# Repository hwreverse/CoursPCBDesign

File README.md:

# CoursPCBDesign
Sources pour les séquences de cours sur Twitch/Youtube (Alexx_and_seb) sur le PCB Design

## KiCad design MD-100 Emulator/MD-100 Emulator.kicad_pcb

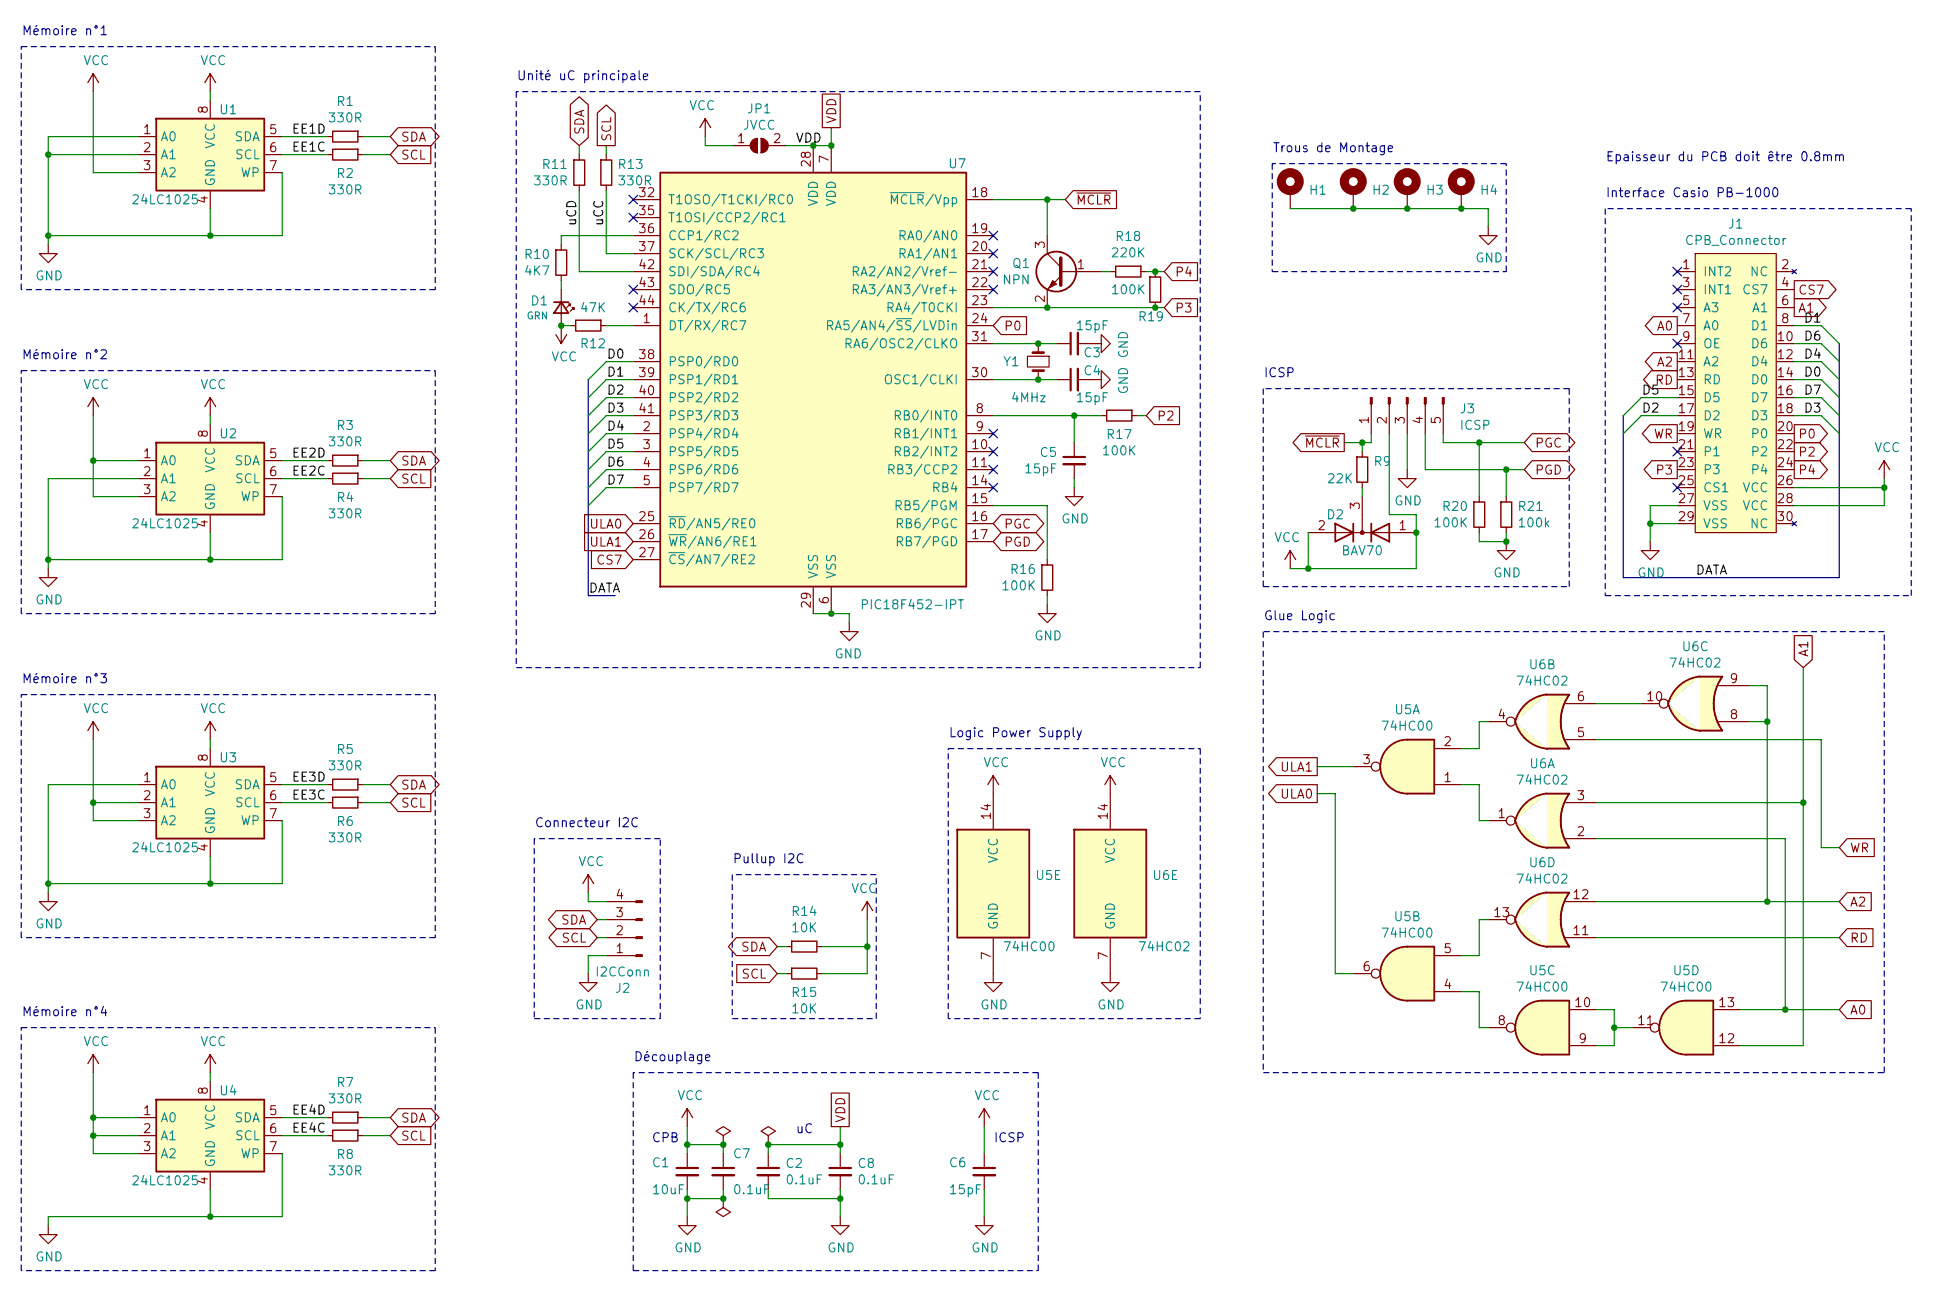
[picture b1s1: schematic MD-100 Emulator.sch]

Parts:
C1: 10uF; C_0805_2012Metric_Pad1.15x1.40mm_HandSolder
C2, C7, C8: 0.1uF; C_0805_2012Metric_Pad1.15x1.40mm_HandSolder
C3, C4, C5, C6: 15pF; C_0805_2012Metric_Pad1.15x1.40mm_HandSolder
D1: GRN; LED_0805_2012Metric_Pad1.15x1.40mm_HandSolder
D2: BAV70; SOT-23
H1, H2, H3, H4: MountingHole_Pad; MountingHole_3.2mm_M3_Pad_Via
J1: CPB_Connector; Connector_Casio_2x15_1.27_SYSBUS
J2: I2CConn; PinHeader_1x04_P2.54mm_Horizontal
J3: ICSP; PinHeader_1x05_P2.54mm_Horizontal
JP1: JVCC; SolderJumper-2_P1.3mm_Open_RoundedPad1.0x1.5mm
Q1: NPN; SOT-23
R1, R2, R3, R4, R5, R6, R7, R8, R11, R13: 330R; R_0805_2012Metric_Pad1.15x1.40mm_HandSolder
R9: 22K; R_0805_2012Metric_Pad1.15x1.40mm_HandSolder
R10: 4K7; R_0805_2012Metric_Pad1.15x1.40mm_HandSolder
R12: 47K; R_0805_2012Metric_Pad1.15x1.40mm_HandSolder
R14, R15: 10K; R_0805_2012Metric_Pad1.15x1.40mm_HandSolder
R16, R17, R19, R20: 100K; R_0805_2012Metric_Pad1.15x1.40mm_HandSolder
R18: 220K; R_0805_2012Metric_Pad1.15x1.40mm_HandSolder
R21: 100k; R_0805_2012Metric_Pad1.15x1.40mm_HandSolder
U1, U2, U3, U4: 24LC1025; SOIC-8_3.9x4.9mm_P1.27mm
U5: 74HC00; SOIC-14_3.9x8.7mm_P1.27mm
U6: 74HC02; SOIC-14_3.9x8.7mm_P1.27mm
U7: PIC18F452-IPT; TQFP-44_10x10mm_P0.8mm
Y1: 4MHz; Crystal_SMD_HC49-SD_HandSoldering

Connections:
/D0: J1.14 (D0), U7.38 (PSP0/RD0)
/D1: J1.8 (D1), U7.39 (PSP1/RD1)
/D2: J1.17 (D2), U7.40 (PSP2/RD2)
/D3: J1.18 (D3), U7.41 (PSP3/RD3)
/D4: J1.12 (D4), U7.2 (PSP4/RD4)
/D5: J1.15 (D5), U7.3 (PSP5/RD5)
/D6: J1.10 (D6), U7.4 (PSP6/RD6)
/D7: J1.16 (D7), U7.5 (PSP7/RD7)
/EE1C: R2.2, U1.6 (SCL)
/EE1D: R1.2, U1.5 (SDA)
/EE2C: R4.2, U2.6 (SCL)
/EE2D: R3.2, U2.5 (SDA)
/EE3C: R6.2, U3.6 (SCL)
/EE3D: R5.2, U3.5 (SDA)
/EE4C: R8.2, U4.6 (SCL)
/EE4D: R7.2, U4.5 (SDA)
/uCC: R13.2, U7.37 (SCK/SCL/RC3)
/uCD: R11.2, U7.42 (SDI/SDA/RC4)
A0: J1.7 (A0), U5.13, U6.2
A1: J1.6 (A1), U5.12, U6.3
A2: J1.11 (A2), U6.8, U6.9, U6.12
CS7: J1.4 (CS7), U7.27 (~CS~/AN7/RE2)
GND: C1.2, C2.2, C3.2, C4.2, C5.2, C6.2, C7.2, C8.2, H1.1, H2.1, H3.1, H4.1, J1.27 (VSS), J1.29 (VSS), J2.1, J3.3, R16.2, R20.2, R21.2, U1.1 (A0), U1.2 (A1), U1.4 (GND), U1.7 (WP), U2.2 (A1), U2.4 (GND), U2.7 (WP), U3.1 (A0), U3.4 (GND), U3.7 (WP), U4.4 (GND), U4.7 (WP), U5.7 (GND), U6.7 (GND), U7.6 (VSS), U7.29 (VSS)
unnamed: C3.1, U7.31 (RA6/OSC2/CLKO), Y1.1
unnamed: C4.1, U7.30 (OSC1/CLKI), Y1.2
unnamed: C5.1, R17.2, U7.8 (RB0/INT0)
unnamed: D1.1 (K), R10.2
unnamed: D2.3 (K), R9.2
unnamed: Q1.1 (B), R18.2
unnamed: R10.1, U7.36 (CCP1/RC2)
unnamed: R12.1, U7.1 (DT/RX/RC7)
unnamed: R16.1, U7.15 (RB5/PGM)
unnamed: U5.1, U6.1
unnamed: U5.2, U6.4
unnamed: U5.4, U5.8
unnamed: U5.5, U6.13
unnamed: U5.9, U5.10, U5.11
unnamed: U6.6, U6.10
P0: J1.20 (P0), U7.24 (RA5/AN4/~SS~/LVDin)
P2: J1.22 (P2), R17.1
P3: J1.23 (P3), Q1.2 (E), R19.2, U7.23 (RA4/T0CKI)
P4: J1.24 (P4), R18.1, R19.1
PGC: J3.5, R20.1, U7.16 (RB6/PGC)
PGD: J3.4, R21.1, U7.17 (RB7/PGD)
RD: J1.13 (RD), U6.11
SCL: J2.2, R2.1, R4.1, R6.1, R8.1, R13.1, R15.1
SDA: J2.3, R1.1, R3.1, R5.1, R7.1, R11.1, R14.1
ULA0: U5.6, U7.25 (~RD~/AN5/RE0)
ULA1: U5.3, U7.26 (~WR~/AN6/RE1)
VCC: C1.1, C6.1, C7.1, D1.2 (A), D2.1 (A), D2.2 (A), J1.26 (VCC), J1.28 (VCC), J2.4, J3.2, JP1.1 (A), R12.2, R14.2, R15.2, U1.3 (A2), U1.8 (VCC), U2.1 (A0), U2.3 (A2), U2.8 (VCC), U3.2 (A1), U3.3 (A2), U3.8 (VCC), U4.1 (A0), U4.2 (A1), U4.3 (A2), U4.8 (VCC), U5.14 (VCC), U6.14 (VCC)
VDD: C2.1, C8.1, JP1.2 (B), U7.7 (VDD), U7.28 (VDD)
WR: J1.19 (WR), U6.5
~MCLR: J3.1, Q1.3 (C), R9.1, U7.18 (~MCLR~/Vpp)

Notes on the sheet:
Mémoire n°1
Mémoire n°2
Mémoire n°3
Mémoire n°4
Glue Logic
Découplage
Connecteur I2C
Logic Power Supply
Interface Casio PB-1000
ICSP
Pullup I2C
Unité uC principale
Trous de Montage
CPB
Epaisseur du PCB doit être 0.8mm

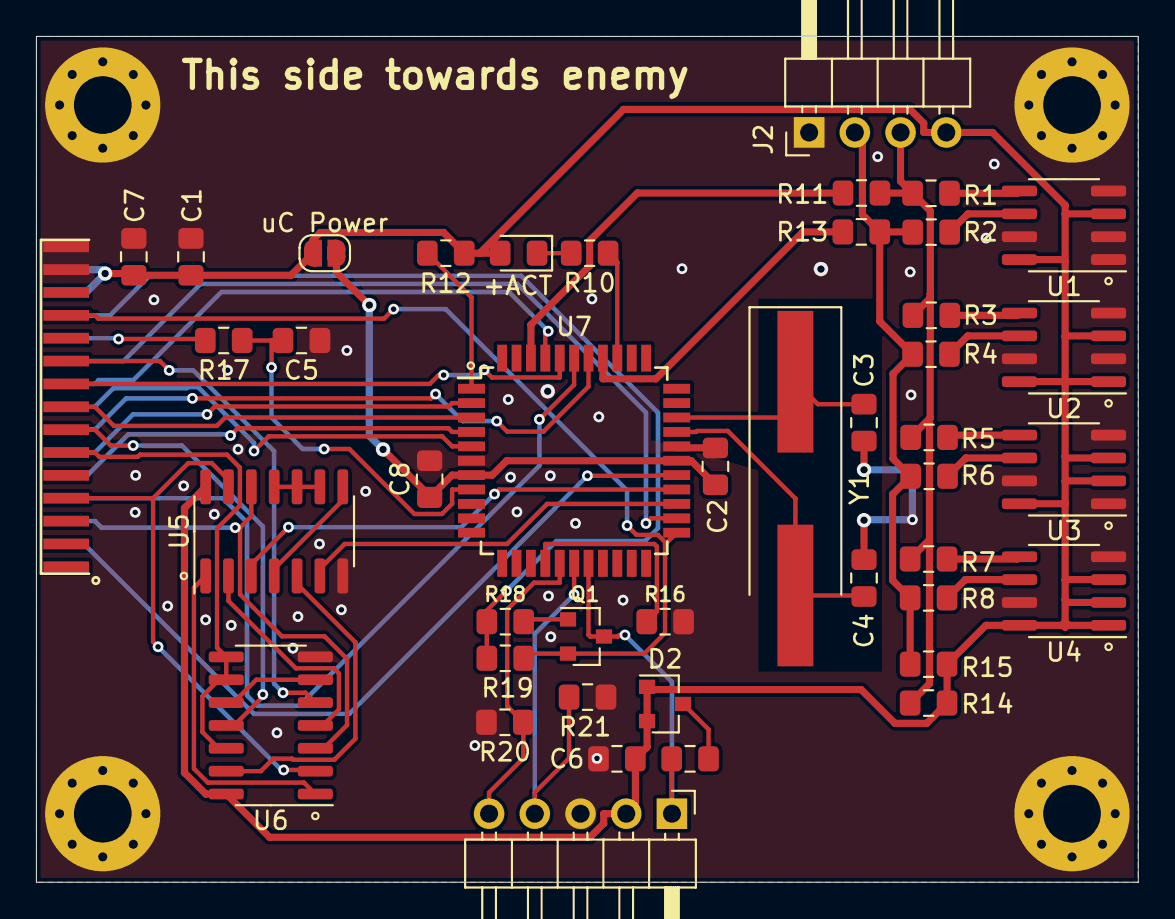
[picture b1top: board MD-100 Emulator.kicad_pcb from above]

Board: 2 copper layers, 61.2 x 47.0 mm, 48 parts (0 on the bottom side), 53 nets.

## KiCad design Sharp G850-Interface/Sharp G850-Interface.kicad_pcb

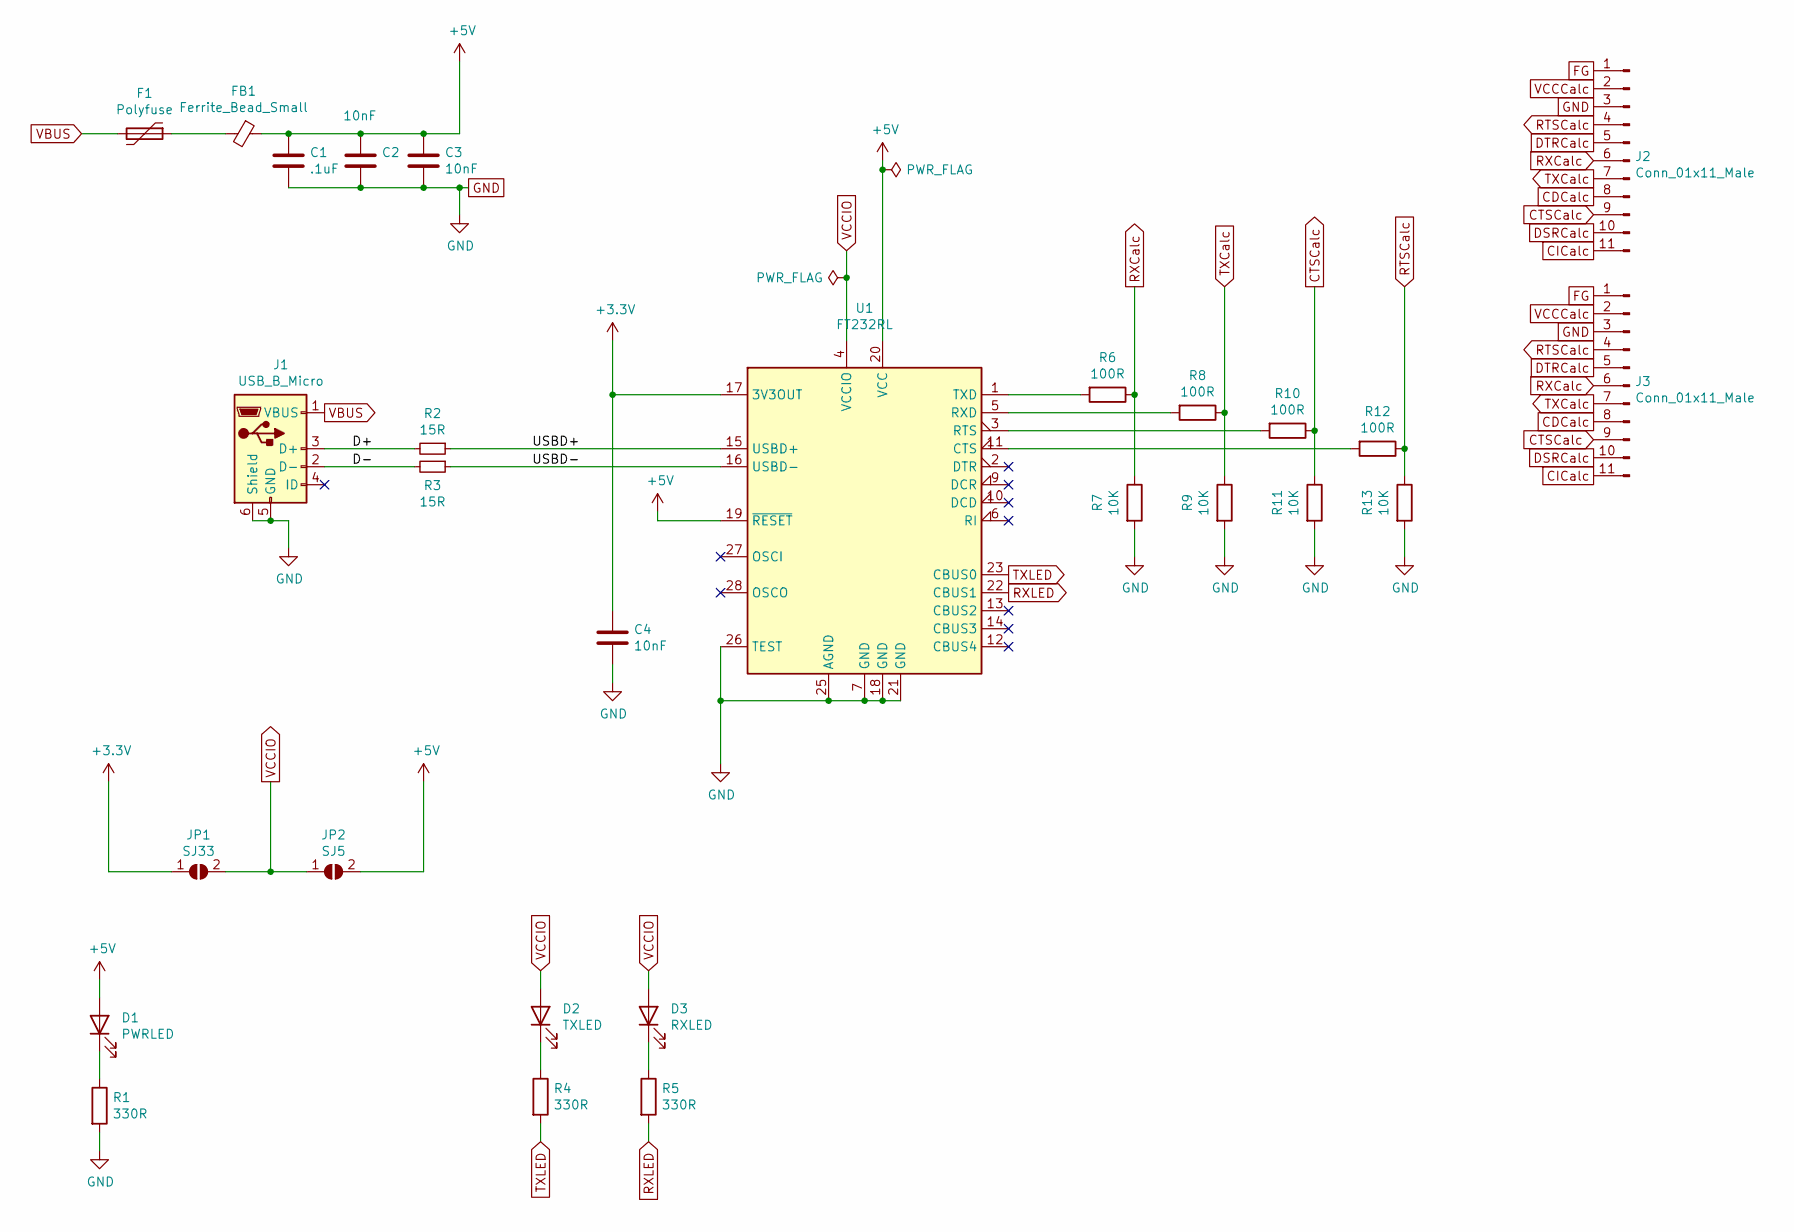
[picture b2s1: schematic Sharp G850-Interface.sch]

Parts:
C1: .1uF; C_0805_2012Metric_Pad1.15x1.40mm_HandSolder
C2, C3, C4: 10nF; C_0805_2012Metric_Pad1.15x1.40mm_HandSolder
D1: PWRLED; LED_0805_2012Metric_Pad1.15x1.40mm_HandSolder
D2: TXLED; LED_0805_2012Metric_Pad1.15x1.40mm_HandSolder
D3: RXLED; LED_0805_2012Metric_Pad1.15x1.40mm_HandSolder
F1: Polyfuse; R_1210_3225Metric_Pad1.42x2.65mm_HandSolder
FB1: Ferrite_Bead_Small; L_0805_2012Metric_Pad1.15x1.40mm_HandSolder
J1: USB_B_Micro; USB_Micro-B_Molex-105017-0001
J2: Conn_01x11_Male; PinHeader_1x11_P2.54mm_Horizontal
J3: Conn_01x11_Male; PinHeader_1x11_P2.54mm_Vertical
JP1: SJ33; SolderJumper-2_P1.3mm_Open_RoundedPad1.0x1.5mm
JP2: SJ5; SolderJumper-2_P1.3mm_Open_RoundedPad1.0x1.5mm
R1, R4, R5: 330R; R_0805_2012Metric_Pad1.15x1.40mm_HandSolder
R2, R3: 15R; R_0805_2012Metric_Pad1.15x1.40mm_HandSolder
R6, R8, R10, R12: 100R; R_0805_2012Metric_Pad1.15x1.40mm_HandSolder
R7, R9, R11, R13: 10K; R_0805_2012Metric_Pad1.15x1.40mm_HandSolder
U1: FT232RL; SSOP-28_5.3x10.2mm_P0.65mm

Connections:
+3V3: C4.1, JP1.1 (A), U1.17 (3V3OUT)
+5V: C1.1, C2.1, C3.1, D1.2 (A), FB1.1, JP2.2 (B), U1.19 (~RESET~), U1.20 (VCC)
/D+: J1.3 (D+), R2.2
/D-: J1.2 (D-), R3.2
/USBD+: R2.1, U1.15 (USBD+)
/USBD-: R3.1, U1.16 (USBD-)
CDCalc: J2.8, J3.8
CICalc: J2.11, J3.11
CTSCalc: J2.9, J3.9, R10.1, R11.1
DSRCalc: J2.10, J3.10
DTRCalc: J2.5, J3.5
FG: J2.1, J3.1
GND: C1.2, C2.2, C3.2, C4.2, J1.5 (GND), J1.6 (Shield), J2.3, J3.3, R1.2, R7.2, R9.2, R11.2, R13.2, U1.7 (GND), U1.18 (GND), U1.21 (GND), U1.25 (AGND), U1.26 (TEST)
unnamed: D1.1 (K), R1.1
unnamed: D2.1 (K), R4.1
unnamed: D3.1 (K), R5.1
unnamed: F1.1, FB1.2
unnamed: R6.2, U1.1 (TXD)
unnamed: R8.2, U1.5 (RXD)
unnamed: R10.2, U1.3 (RTS)
unnamed: R12.2, U1.11 (CTS)
RTSCalc: J2.4, J3.4, R12.1, R13.1
RXCalc: J2.6, J3.6, R6.1, R7.1
RXLED: R5.2, U1.22 (CBUS1)
TXCalc: J2.7, J3.7, R8.1, R9.1
TXLED: R4.2, U1.23 (CBUS0)
VBUS: F1.2, J1.1 (VBUS)
VCCCalc: J2.2, J3.2
VCCIO: D2.2 (A), D3.2 (A), JP1.2 (B), JP2.1 (A), U1.4 (VCCIO)

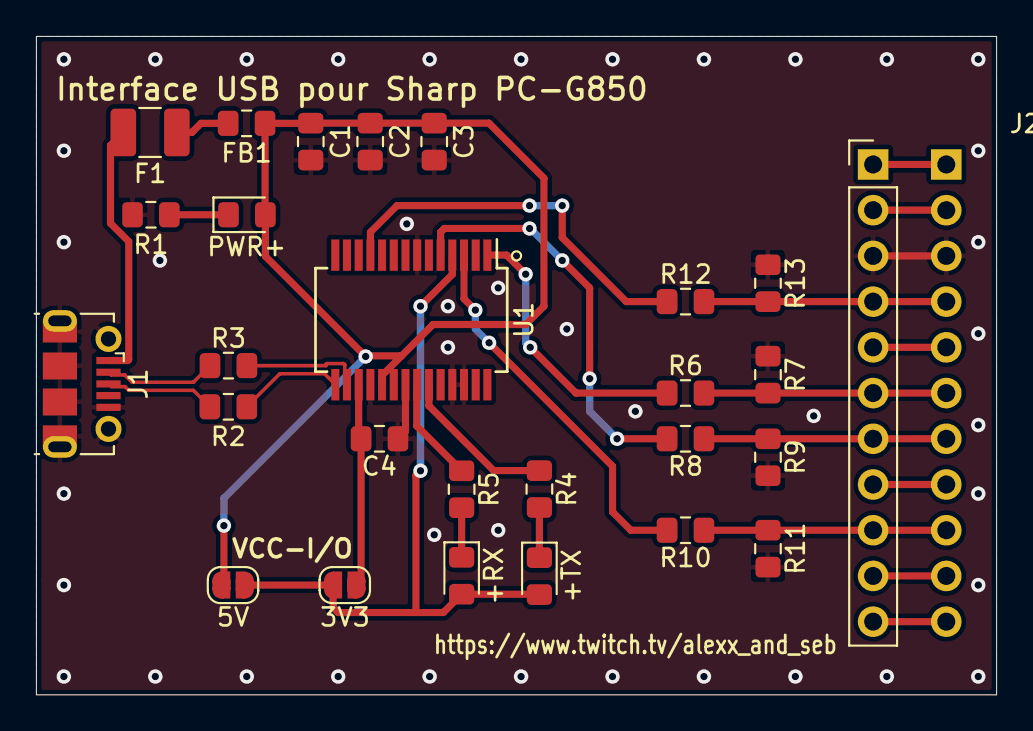
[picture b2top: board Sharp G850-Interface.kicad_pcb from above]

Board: 2 copper layers, 53.3 x 36.6 mm, 28 parts (0 on the bottom side), 29 nets.

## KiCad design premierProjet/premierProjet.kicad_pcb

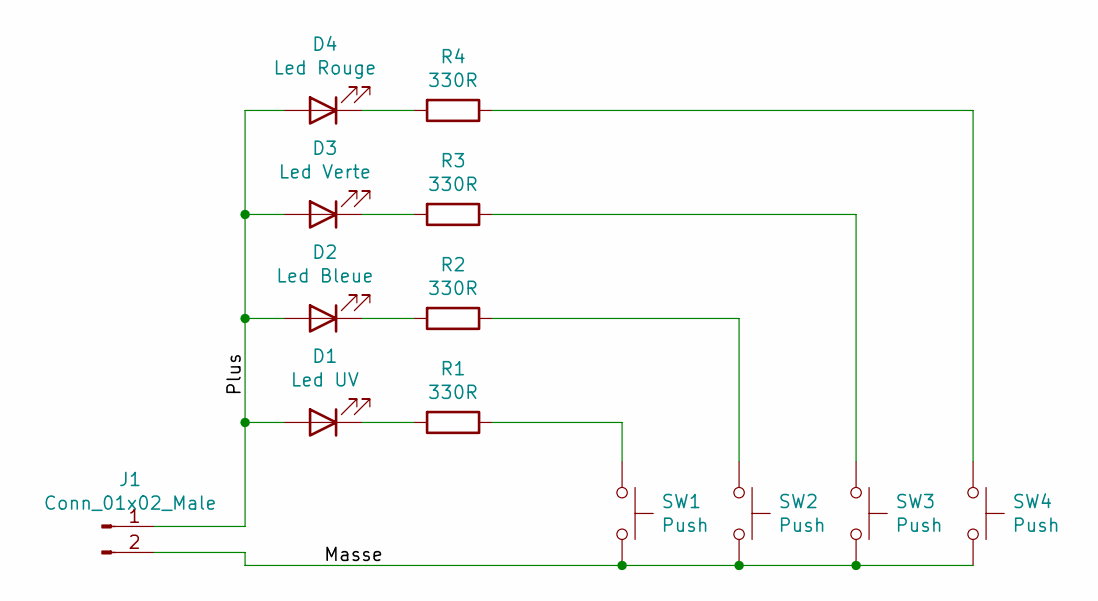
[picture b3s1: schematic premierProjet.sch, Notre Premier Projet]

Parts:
D1: Led UV; LED_0805_2012Metric_Pad1.15x1.40mm_HandSolder
D2: Led Bleue; LED_0805_2012Metric_Pad1.15x1.40mm_HandSolder
D3: Led Verte; LED_0805_2012Metric_Pad1.15x1.40mm_HandSolder
D4: Led Rouge; LED_0805_2012Metric_Pad1.15x1.40mm_HandSolder
J1: Conn_01x02_Male; PinHeader_1x02_P2.54mm_Horizontal
R1, R2, R3, R4: 330R; R_0805_2012Metric_Pad1.15x1.40mm_HandSolder
SW1, SW2, SW3, SW4: Push; SW_PUSH_6mm

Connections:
/Masse: J1.2, SW1.2, SW2.2, SW3.2, SW4.2
/Plus: D1.2 (A), D2.2 (A), D3.2 (A), D4.2 (A), J1.1
unnamed: D1.1 (K), R1.2
unnamed: D2.1 (K), R2.2
unnamed: D3.1 (K), R3.2
unnamed: D4.1 (K), R4.2
unnamed: R1.1, SW1.1
unnamed: R2.1, SW2.1
unnamed: R3.1, SW3.1
unnamed: R4.1, SW4.1

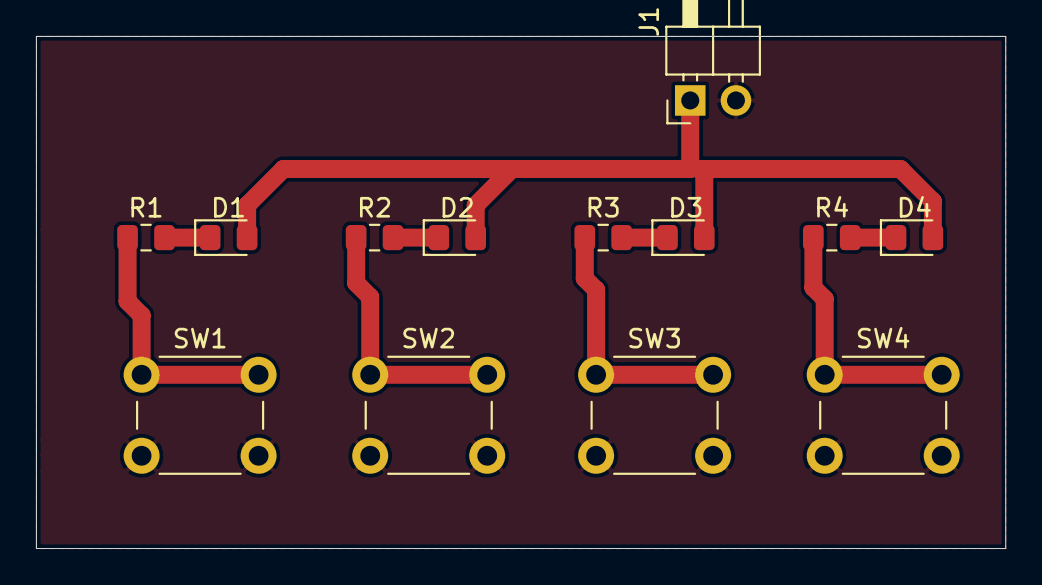
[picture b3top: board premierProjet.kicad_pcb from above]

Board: 2 copper layers, 53.8 x 28.4 mm, 13 parts (0 on the bottom side), 10 nets.

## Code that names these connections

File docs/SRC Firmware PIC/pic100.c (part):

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 read from the EEPROM when too high) */

/* port pins */
#define	SDA	RC4	/* I2C bus */
#define	SCL	RC3	/* I2C bus */
#define	GRN_LED	RC2	/* green LED driven in the PWM mode (CCP1) */
#define	PGMDATA	RB7	/* programming mode data input/output */
#define	PGMCLK	RB6	/* programming mode clock input */
#define	FD_DIR	RB0	/* transfer direction strobe signal input (P2) */
#define	FD_ACK	RA5	/* transfer direction acknowledge signal output (P0) */
#define	FD_PWR	RA4	/* power control signal input (P3) */


#pragma udata udata1
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
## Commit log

2020-05-08 commit premier Projet (YOLO)
2020-05-09 Added docs+ /docs
2020-05-10 Added G850 Kiss schema
2020-05-10 Created G850 Project
2020-05-11 Finished G850 Schema
2020-05-11 Added 4 eeproms in md100
2020-05-11 Added Kicad Hotkeys
2020-05-11 j'ai enlevé un bout de ficelle qui gênait
2020-05-11 Added 24LC1025.pdf documentation
2020-05-14 cours pcb alexx08
    merci max de me le rappeller
2020-05-15 Temp save
2020-05-15 Added Pic + Bus + quartz
2020-05-15 Added PIC Firmware sources
2020-05-16 MD-100 Terminé et annoté
    à vérifier au minimum 1 fois encore
2020-05-17 Correction en cours du md1000
    (pas le proj optimité fait en offline
2020-05-17 PCB du prmierProjet
2020-05-19 PCB Complet pour premier projet
    YOLO
2020-05-20 Routage PCB Interface G850
2020-05-21 Finished PCB + Added gerber files
2020-05-21 + step model + footprints
    added the molex step model, and the g850 1x11 pinheader without silkscreen footprint
2020-05-23 Amélioré MD100 Emulator
2020-05-23 Autoroutage de MD100 Version 1
2020-05-27 Routage du PCB MD-100 terminé
2020-06-01 Premier commit sur carte son
2020-06-01 update du connecteur audio
2020-06-20 debut cours n°18
2020-06-20 cours du 20.06.2020 fin
2020-06-22 Cours du 22.06.2020
2020-07-03 carte son opll cours final
